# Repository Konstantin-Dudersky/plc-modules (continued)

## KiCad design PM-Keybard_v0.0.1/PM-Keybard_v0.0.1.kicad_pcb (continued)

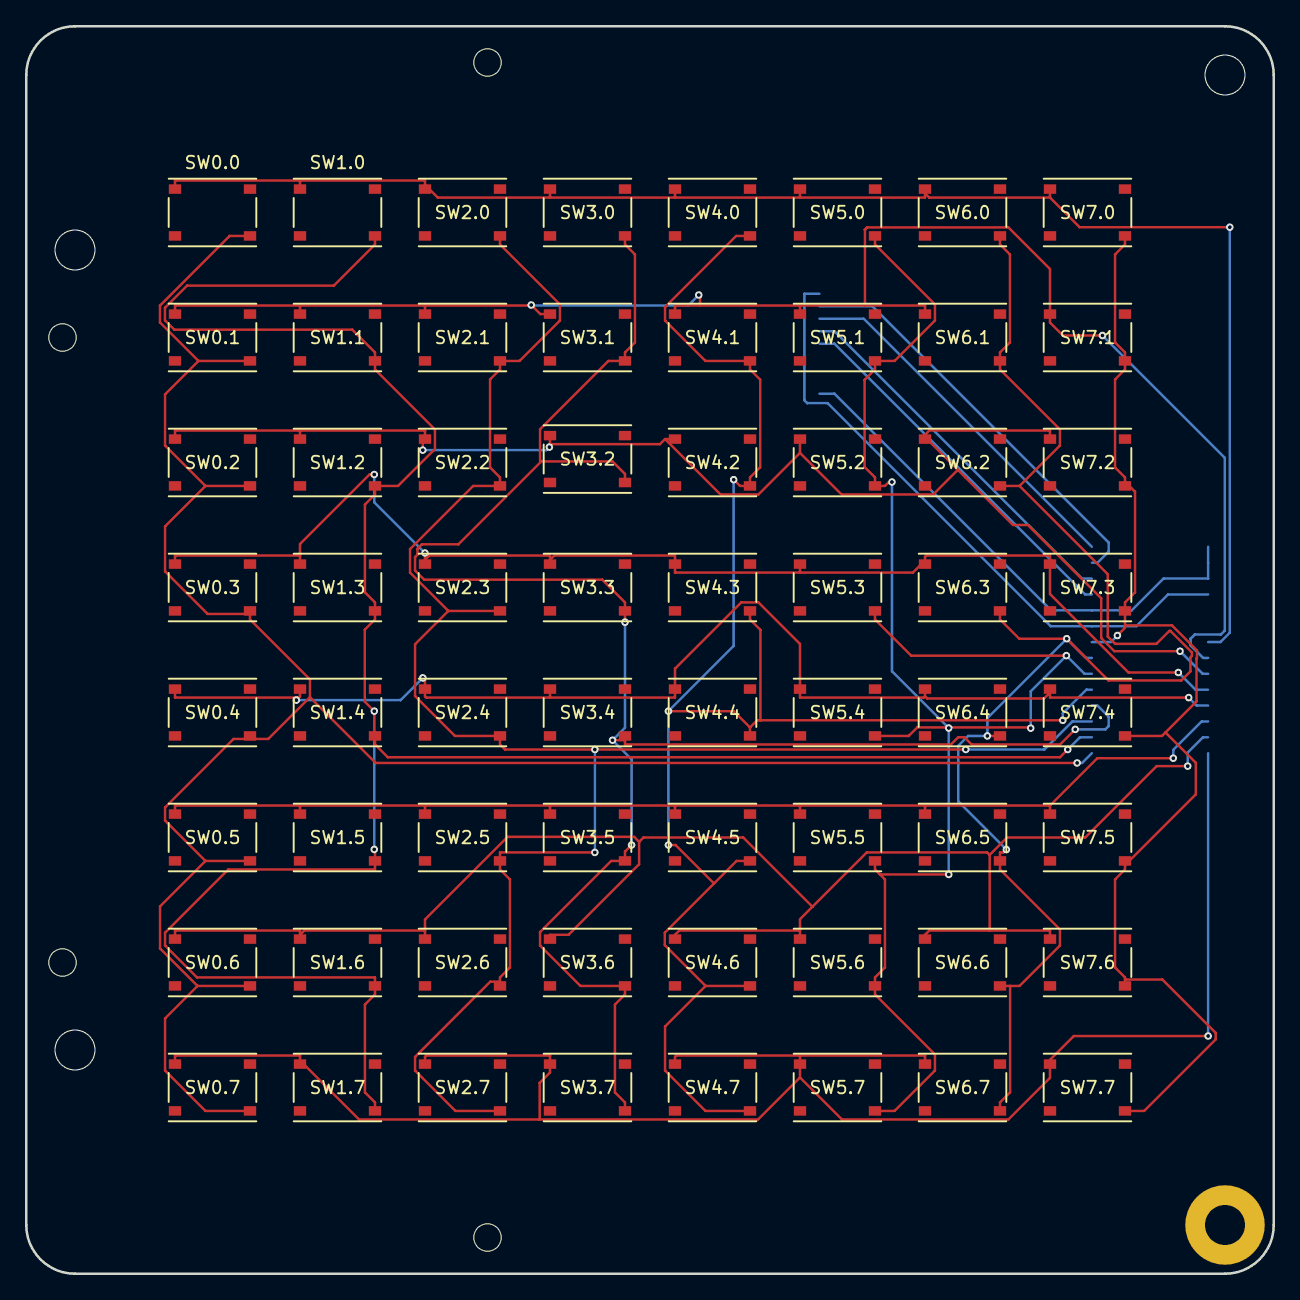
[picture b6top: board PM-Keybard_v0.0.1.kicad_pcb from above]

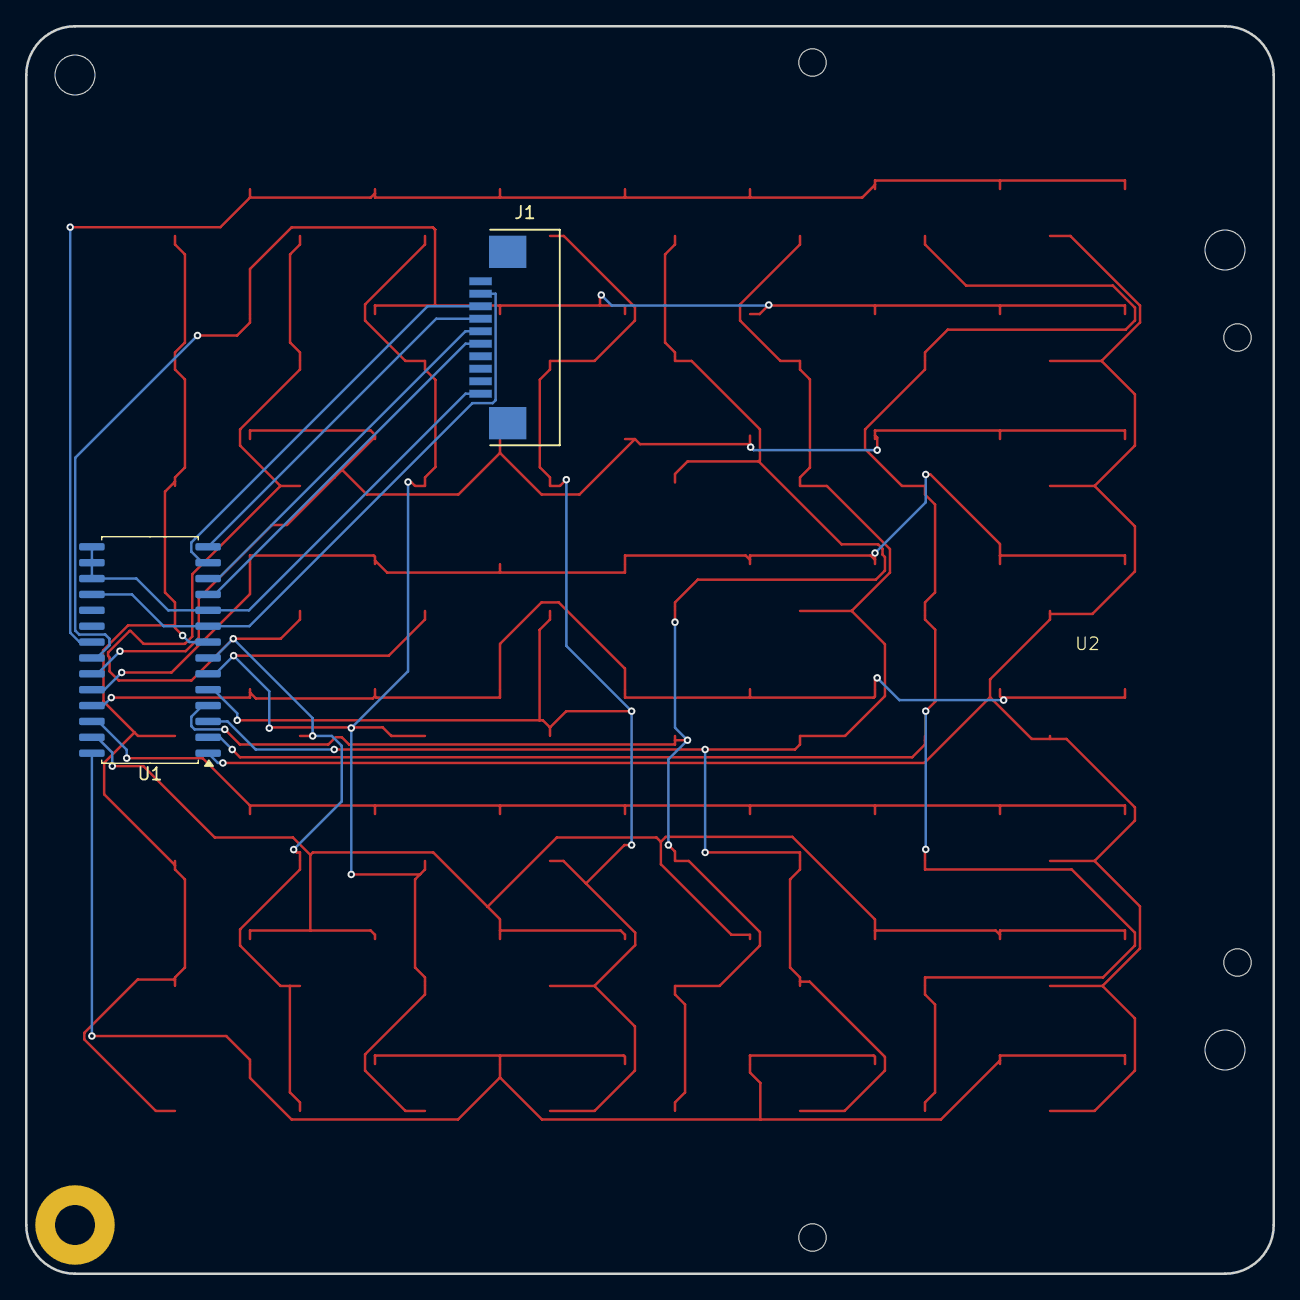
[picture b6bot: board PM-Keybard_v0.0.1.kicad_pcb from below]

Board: 2 copper layers, 99.8 x 99.8 mm, 71 parts (3 on the bottom side), 22 nets.
